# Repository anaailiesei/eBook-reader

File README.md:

# OpenBook

## 1. Diagrama Bloc

## 2. BOM
|DEVICE                                                  |PARTS                                                                                                  |PURCHASE URL                                                                                                                                      |DATASHEET URL                                                                                                                                     |
|--------------------------------------------------------|-------------------------------------------------------------------------------------------------------|--------------------------------------------------------------------------------------------------------------------------------------------------|--------------------------------------------------------------------------------------------------------------------------------------------------|
|ADAFRUIT_LEDCHIP-LED0603                                |CHG_LED                                                                                                |https://www.tme.eu/en/details/kp-1608surck/smd-colour-leds/kingbright-electronic/                                                                 |https://www.alldatasheet.com/datasheet-pdf/pdf/1153370/TO-GRACE/KP-1608SURCK.html                                                                 |
|EAGLE-LTSPICE_C                                         |EPD_C5                                                                                                 |https://www.digikey.com/en/products/detail/samsung-electro-mechanics/CL05B104KB5NNNC/11696318                                                     |https://www.digikey.com/en/products/detail/samsung-electro-mechanics/CL05B104KB5NNNC/11696318                                                     |
|ESP32_WROVER_EAGLE-LTSPICE_R                            |R3                                                                                                     |https://www.digikey.com/en/products/detail/cts-resistor-products/73L1R47J/1543472                                                                 |https://www.digikey.com/en/products/detail/cts-resistor-products/73L1R47J/1543472                                                                 |
|ESP32_WROVER_EAGLE-LTSPICE_R                            |R1_PWRUSB                                                                                              |https://www.digikey.com/en/products/detail/yageo/RC0402JR-07100KL/726416                                                                          |https://www.digikey.com/en/products/detail/yageo/RC0402JR-07100KL/726416                                                                          |
|EAGLE-LTSPICE_C                                         |C1, C2, C4_USB, C6, C8, C9, C10, C_DELAY                                                               |https://www.digikey.com/en/products/detail/samsung-electro-mechanics/CL05B104KP5NNNC/3886660                                                      |https://www.digikey.com/en/products/detail/samsung-electro-mechanics/CL05B104KP5NNNC/3886660                                                      |
|RCL_CPOL-EUCT3528                                       |C3                                                                                                     |https://ro.mouser.com/ProductDetail/KEMET/T491B107K006AT?qs=0CYHZL%252BGkuR7Fv7IsnkA2g%3D%3D                                                      |https://ro.mouser.com/ProductDetail/KEMET/T491B107K006AT?qs=0CYHZL%252BGkuR7Fv7IsnkA2g%3D%3D                                                      |
|ESP32_WROVER_EAGLE-LTSPICE_R                            |R1, R1_PINH, R1_PINH1, R2_PINH, R2_PINH1, R4, R5, R6, R7, R8, R9, R10, R_BOOT, R_CHANGE, R_CL1, R_RESET|https://www.digikey.com/en/products/detail/yageo/RC0402JR-0710KL/726418                                                                           |https://www.digikey.com/en/products/detail/yageo/RC0402JR-0710KL/726418                                                                           |
|EAGLE-LTSPICE_C                                         |C7                                                                                                     |https://www.digikey.com/en/products/detail/samsung-electro-mechanics/CL05A106MP5NUNC/3887108                                                      |https://www.digikey.com/en/products/detail/samsung-electro-mechanics/CL05A106MP5NUNC/3887108                                                      |
|112A-TAAR-R03_ATTEND                                    |J4                                                                                                     |https://www.digikey.com/en/products/detail/attend-technology/112A-TAAR-R03/17633923?s=N4IgTCBcDaIIxzAQQLQBUlIEoqwBgGYQBdAXyA                      |https://www.digikey.com/en/products/detail/attend-technology/112A-TAAR-R03/17633923?s=N4IgTCBcDaIIxzAQQLQBUlIEoqwBgGYQBdAXyA                      |
|ESP32_WROVER_EAGLE-LTSPICE_R                            |R_CAPACITOR                                                                                            |https://www.digikey.com/en/products/detail/te-connectivity-passive-product/CRGCQ0402F15R/8576207                                                  |https://www.digikey.com/en/products/detail/te-connectivity-passive-product/CRGCQ0402F15R/8576207                                                  |
|EAGLE-LTSPICE_C                                         |C5                                                                                                     |https://www.digikey.com/en/products/detail/taiyo-yuden/JMK105BJ105KV-F/930583                                                                     |https://www.digikey.com/en/products/detail/taiyo-yuden/JMK105BJ105KV-F/930583                                                                     |
|EAGLE-LTSPICE_C                                         |EPD_C1, EPD_C2, EPD_C3, EPD_C4, EPD_C6, EPD_C7, EPD_C8, EPD_C9, EPD_C10                                |https://www.digikey.com/en/products/detail/murata-electronics/GRM155R61H105KE05D/13531808                                                         |https://www.digikey.com/en/products/detail/murata-electronics/GRM155R61H105KE05D/13531808                                                         |
|ESP32_WROVER_EAGLE-LTSPICE_R                            |R2                                                                                                     |https://www.digikey.com/en/products/detail/stackpole-electronics-inc/RMCF0402FT2R20/4376617                                                       |https://www.digikey.com/en/products/detail/stackpole-electronics-inc/RMCF0402FT2R20/4376617                                                       |
|ESP32_WROVER_EAGLE-LTSPICE_R                            |R1_BAT                                                                                                 |https://www.digikey.com/en/products/detail/panasonic-electronic-components/ERJ-2RKF2000X/192215                                                   |https://www.digikey.com/en/products/detail/panasonic-electronic-components/ERJ-2RKF2000X/192215                                                   |
|ESP32_WROVER_SPARKFUN-DISCRETESEMI_MOSFET_PCH           |Q1, Q2                                                                                                 |https://ro.mouser.com/ProductDetail/Diodes-Incorporated/DMG2305UXQ-7?qs=60RJRzIpcl%2FUiAojHt1c9w%3D%3D                                            |https://ro.mouser.com/ProductDetail/Diodes-Incorporated/DMG2305UXQ-7?qs=60RJRzIpcl%2FUiAojHt1c9w%3D%3D                                            |
|ESP32_WROVER_EAGLE-LTSPICE_R                            |R2_BAT                                                                                                 |https://www.digikey.com/en/products/detail/panasonic-electronic-components/ERJ-2RKF2001X/192194                                                   |https://www.digikey.com/en/products/detail/panasonic-electronic-components/ERJ-2RKF2001X/192194                                                   |
|EAGLE-LTSPICE_C                                         |C1_BAT, C1_BAT1, C1_BAT2, C2_BAT, C5_USB                                                               |https://www.digikey.com/en/products/detail/samsung-electro-mechanics/CL05A475KQ5NRNC/3887139                                                      |https://www.digikey.com/en/products/detail/samsung-electro-mechanics/CL05A475KQ5NRNC/3887139                                                      |
|EAGLE-LTSPICE_C                                         |C4                                                                                                     |https://www.digikey.com/en/products/detail/murata-electronics/GRM155C61E475ME15D/16821133                                                         |https://www.digikey.com/en/products/detail/murata-electronics/GRM155C61E475ME15D/16821133                                                         |
|ESP32_WROVER_EAGLE-LTSPICE_R                            |R2-USB, R2-USB1                                                                                        |https://www.digikey.com/en/products/detail/panasonic-electronic-components/ERA-2AEB512X/1706022                                                   |https://www.digikey.com/en/products/detail/panasonic-electronic-components/ERA-2AEB512X/1706022                                                   |
|744043680IND_4828-WE-TPC_WRE                            |L1                                                                                                     |https://www.digikey.com/en/products/detail/w%C3%BCrth-elektronik/744043680/1638515?s=N4IgTCBcDaIOwBYEAYEGYBsAOZIC6AvkA                            |https://www.digikey.com/en/products/detail/w%C3%BCrth-elektronik/744043680/1638515?s=N4IgTCBcDaIOwBYEAYEGYBsAOZIC6AvkA                            |
|BD5229G-TR                                              |IC1                                                                                                    |https://www.digikey.com/en/products/detail/rohm-semiconductor/BD5229G-TR/658502?s=N4IgTCBcDaIEIBECsYwE4DiBaAKgJRAF0BfIA                           |https://www.digikey.com/en/products/detail/rohm-semiconductor/BD5229G-TR/658502?s=N4IgTCBcDaIEIBECsYwE4DiBaAKgJRAF0BfIA                           |
|ESP32_WROVER_BME680_BME680                              |SENSOR2                                                                                                |https://www.digikey.com/en/products/detail/bosch-sensortec/BME680/7401317                                                                         |https://www.digikey.com/en/products/detail/bosch-sensortec/BME680/7401317                                                                         |
|BUTTON_CUSYOMV1.                                        |BOOT_BUTTON, CHANGE_BUTTON, RESET_BUTTON                                                               |https://www.digikey.com/en/products/detail/c-k/KMS221G-LFS/2043218?s=N4IgTCBcDaINIFkDKYwEYDiAZAYkkAugL5A                                          |https://www.digikey.com/en/products/detail/c-k/KMS221G-LFS/2043218?s=N4IgTCBcDaINIFkDKYwEYDiAZAYkkAugL5A                                          |
|CPH3225A                                                |C10_SUPERCAP                                                                                           |https://www.snapeda.com/api/url_track_click_mouser/?unipart_id=562593&manufacturer=Seiko Instruments&part_name=CPH3225A&search_term=None          |https://www.snapeda.com/api/url_track_click_mouser/?unipart_id=562593&manufacturer=Seiko Instruments&part_name=CPH3225A&search_term=None          |
|DS3231SN#                                               |U3                                                                                                     |https://www.snapeda.com/api/url_track_click_mouser/?unipart_id=99048&manufacturer=Analog Devices&part_name=DS3231SN#&search_term=None             |https://www.snapeda.com/api/url_track_click_mouser/?unipart_id=99048&manufacturer=Analog Devices&part_name=DS3231SN#&search_term=None             |
|ESP32-C6-WROOM-1-N8                                     |U2                                                                                                     |https://www.digikey.com/en/products/detail/espressif-systems/ESP32-C6-WROOM-1-N8/17728866?s=N4IgTCBcDaIKIGUAKBmMBaAwgNnQdQCUB5IgWXQEZ0A5ADhAF0BfIA|https://www.digikey.com/en/products/detail/espressif-systems/ESP32-C6-WROOM-1-N8/17728866?s=N4IgTCBcDaIKIGUAKBmMBaAwgNnQdQCUB5IgWXQEZ0A5ADhAF0BfIA|
|ESP32C6_VARISTORCN1812                                  |PFMF.050.1                                                                                             |https://www.digikey.com/en/products/detail/epcos-tdk-electronics/B72580T0400K062/4945372                                                          |https://www.digikey.com/en/products/detail/epcos-tdk-electronics/B72580T0400K062/4945372                                                          |
|ESP32_WROVER_AVX---SD0805S020S1R0_AVX_SD0805S020S1R0_0_0|D2                                                                                                     |https://www.digikey.com/en/products/detail/kyocera-avx/SD0805S020S1R0/3749517?s=N4IgTCBcDaIMoBEAMAOJBWOSxLgRgCUkQBdAXyA                           |https://www.digikey.com/en/products/detail/kyocera-avx/SD0805S020S1R0/3749517?s=N4IgTCBcDaIMoBEAMAOJBWOSxLgRgCUkQBdAXyA                           |
|ESP32_WROVER_SPARKFUN-IC-POWER_MCP73831                 |MCP73831                                                                                               |https://www.digikey.com/en/products/detail/microchip-technology/MCP73831T-2ACI-OT/964301                                                          |https://www.digikey.com/en/products/detail/microchip-technology/MCP73831T-2ACI-OT/964301                                                          |
|FH34SRJ-24S-0.5SH_99_                                   |J1                                                                                                     |https://www.digikey.com/en/products/detail/hirose-electric-co-ltd/fh34srj-24s-0-5sh-99/5132529                                                    |https://www.digikey.com/en/products/detail/hirose-electric-co-ltd/fh34srj-24s-0-5sh-99/5132529                                                    |
|MAX17048G+T10                                           |U4                                                                                                     |https://www.snapeda.com/api/url_track_click_mouser/?unipart_id=329239&manufacturer=Analog Devices&part_name=MAX17048G+T10&search_term=None        |https://www.digikey.com/en/products/detail/analog-devices-inc-maxim-integrated/max17048g-t10/3758921                                              |
|MBR0530.                                                |D3, D4, D5                                                                                             |https://www.digikey.com/en/products/detail/smc-diode-solutions/MBR0530/16692306                                                                   |https://www.digikey.com/en/products/detail/smc-diode-solutions/MBR0530/16692306                                                                   |
|PGB1010603MR.                                           |D6, D8, D9, D10, D11, D12                                                                              |https://www.digikey.com/en/products/detail/littelfuse-inc/PGB1010603MR/715755                                                                     |https://www.digikey.com/en/products/detail/littelfuse-inc/PGB1010603MR/715755                                                                     |
|QWIIC_CONNECTORJS-1MM                                   |J3                                                                                                     |https://www.digikey.lt/en/products/detail/jst-sales-america-inc/SM04B-SRSS-TB/926710                                                              |https://www.digikey.lt/en/products/detail/jst-sales-america-inc/SM04B-SRSS-TB/926710                                                              |
|SAMACSYS_PARTS_USB4110-GF-A                             |J2                                                                                                     |https://www.digikey.lt/en/products/detail/gct/usb4110-gf-a/10384547                                                                               |https://www.digikey.lt/en/products/detail/gct/usb4110-gf-a/10384547                                                                               |
|ESP32_WROVER_AVX---SD0805S020S1R0_AVX_SD0805S020S1R0_0_0|D7                                                                                                     |https://www.digikey.lt/en/products/detail/kyocera-avx/sd0805s020s1r0/3749517                                                                      |https://www.digikey.lt/en/products/detail/kyocera-avx/sd0805s020s1r0/3749517                                                                      |
|SI1308EDL-T1-GE3                                        |Q3                                                                                                     |https://www.digikey.lt/en/products/detail/vishay-siliconix/si1308edl-t1-ge3/4876435                                                               |https://www.digikey.lt/en/products/detail/vishay-siliconix/si1308edl-t1-ge3/4876435                                                               |
|USBLC6-2SC6Y                                            |D1                                                                                                     |https://www.digikey.lt/en/products/detail/stmicroelectronics/usblc6-2sc6y/2819177                                                                 |https://www.digikey.lt/en/products/detail/stmicroelectronics/usblc6-2sc6y/2819177                                                                 |
|W25Q512JVEIQ                                            |U1                                                                                                     |https://www.digikey.lt/en/products/detail/winbond-electronics/w25q512jveiq/10244706                                                               |https://www.digikey.lt/en/products/detail/winbond-electronics/w25q512jveiq/10244706                                                               |
|XC6220A331MR-G                                          |IC4                                                                                                    |https://www.digikey.lt/en/products/detail/torex-semiconductor-ltd/xc6220a331mr-g/10165775                                                         |https://www.digikey.lt/en/products/detail/torex-semiconductor-ltd/xc6220a331mr-g/10165775                                                         |
|TP                                                      |TP1, TP2, TP3, TP4, TP5, TP6, TP7, TP8, TP9, TP10, TP11, TP12, TP13, TP14, TP15, TP16, TP17            |                                                                                                                                                  |                                                                                                                                                  |
|SJ                                                      |SJ1                                                                                                    |                                                                                                                                                  |                                                                                                                                                  |

## 3. Descrierea în detaliu a funcționalității hardware
| Nume       | Descriere                                                                  | Pini comunicare ESP32-C6     | Comunicare     |
|------------------------|-------------------------------------------------------------------------------|---------------------------|----------------|
| ESP32-C6-WROOM-1       | MCU RISC-V pe 32 de biți la 160MHz, cu memorie SRAM de 512KB + 16KB și flash extern de 8MB                                                    | USB 2.0, SPI, I2C, UART, GPIO | -              |
| 7.5" e-Paper Display   | E-Paper de 7.5 inch, 800x480 pixeli, alb-negru, cu contrast 8:1, refresh rapid (sub 1s)                                             | SPI + CS, DC, RST, BUSY   | SPI            |
| BME688 Sensor          | Senzor  pentru temperatură, umiditate, presiune și calitatea aerului                                  | SDA, SCL       | I2C            |
| MAX17048 Fuel Gauge    | Gestionare baterie                                                         | I2C                       | I2C            |
| MCP73831 Charger       | Gestionare baterie                                                               | GPIO for control          | GPIO           |
| Buttons        | Butoane fizice tactile cu debouncing hardware prin filtre RC                                              | 3x GPIOs                  | GPIO           |
| USB-C Connector        | Pentru încărcare și transfer de date USB 2.0, cu protecție ESD și posibil suport pentru Power Delivery                                  | USB-D+/D- (native USB)    | USB            |
| SD Card Connector      | Pentru memorie                                                              | - | SPI     |
| DS3231 RTC             | Ceas Real Time                                          | I2C                       | I2C            |
| Qwiic/Stemma Connector | Expansiune conector senzori                                               | I2C                | I2C            |
| LDO Voltage Regulator  | Genereaza o singură șină de alimentare de 3.3V                                             | -                         | -          |
| Baterie (2500mAh)      | Baterie Li-Polimer de 2500mAh, 3.7V. Consum redus în deep sleep (sub 50µA) și alimentare de 3.3V pentru sistem                                                  | -                         | -          |

## 4. Asezarea componentelor in carcasa

* PCB-ul are o grosime de 1mm si este sprijinit de capacul carcasei
* Bateria este sprijinita de capacul carcasei
* Ecranul este sprijinit de spatele PCB-ului

## 5. Pasi de implementare
1. Am realizat schematicul cu ajutor componentelor din libraria data si schematicul model.
2. De la schematic am generat PCB-ul 2D. Am adaugat componentele pe PCB conform schemei date.
3. Am facut un nou net class pentru liniile de putere (SupplyNets) si am adaugat liniile corespunzatoare. Am facut o regula speciala pentru grosimea acestor linii (0.3mm).
4. Am rutat manual liniile de putere pentru a ma asigura ca nu folosesc vias-uri prea multe (a fost necesar sa folosesc vias-uri o singura data). Am facut apoi autorutarea.
5. Am adaugat planurile de masa si via stiches.
6. Am adaugat pentru fiecare componenta un model 3D. Am tinut cont la elementele polarizate sau marcate de orientarea componentei pentru o reprezentare cat mai realista.
7. Am modelat bateria si ecranul conform datasheetului si le-am asamblat in carcasa.

## 6. Decizii

* Eroare SMD-Hole (Samacsys-Parts): Am rezolvat mutand gaurile cu 0.1 mm.

* Eroare Copper width SMD (Net Class: SupplyLines): Am modificat pad-urile de la bobina (Ind_4828) sa fie mai mari (0.5 x 0.5 mm) ca sa permita conectarea cu liniile de putere.

* Eroare Copper width SMD (Net Class: SupplyLines): Am modificat pad-urile de la SON50P200X sa fie mai mari (de la 0.27 mm la 0.3 mm) ca sa permita conectarea cu liniile de putere (VBAT).

* Am aprobat erorile de Power Pin ... connected to ... din Schematic.

## 7. Dificultati
* Gasirea modelelor 3D pentru fiecare componenta, actualizarea bibliotecii, aranjarea lor sa se potriveasca cu footprint-ul.
* M-am asigurat ca nu am froarte multe vias-uri la traseele de putere si a trebuit sa fac o parte din rutare manual. Nu am putut evita o situatie (traseele ar fi ajuns sa fie exagerat de lungi din cauza ocolirilor daca nu foloseam) si a fost nevoie sa folosesc vias-uri pe un traseu de putere.
* Desi nu am avut de facut modele 3D complexe, aceasta a fost o provocare deoarece a fost prima data cand am facut asa ceva.
* Verificarea ca traseele sa nu contina unghiuri drepte si corectarea lor.

## 8. Imagini PCB

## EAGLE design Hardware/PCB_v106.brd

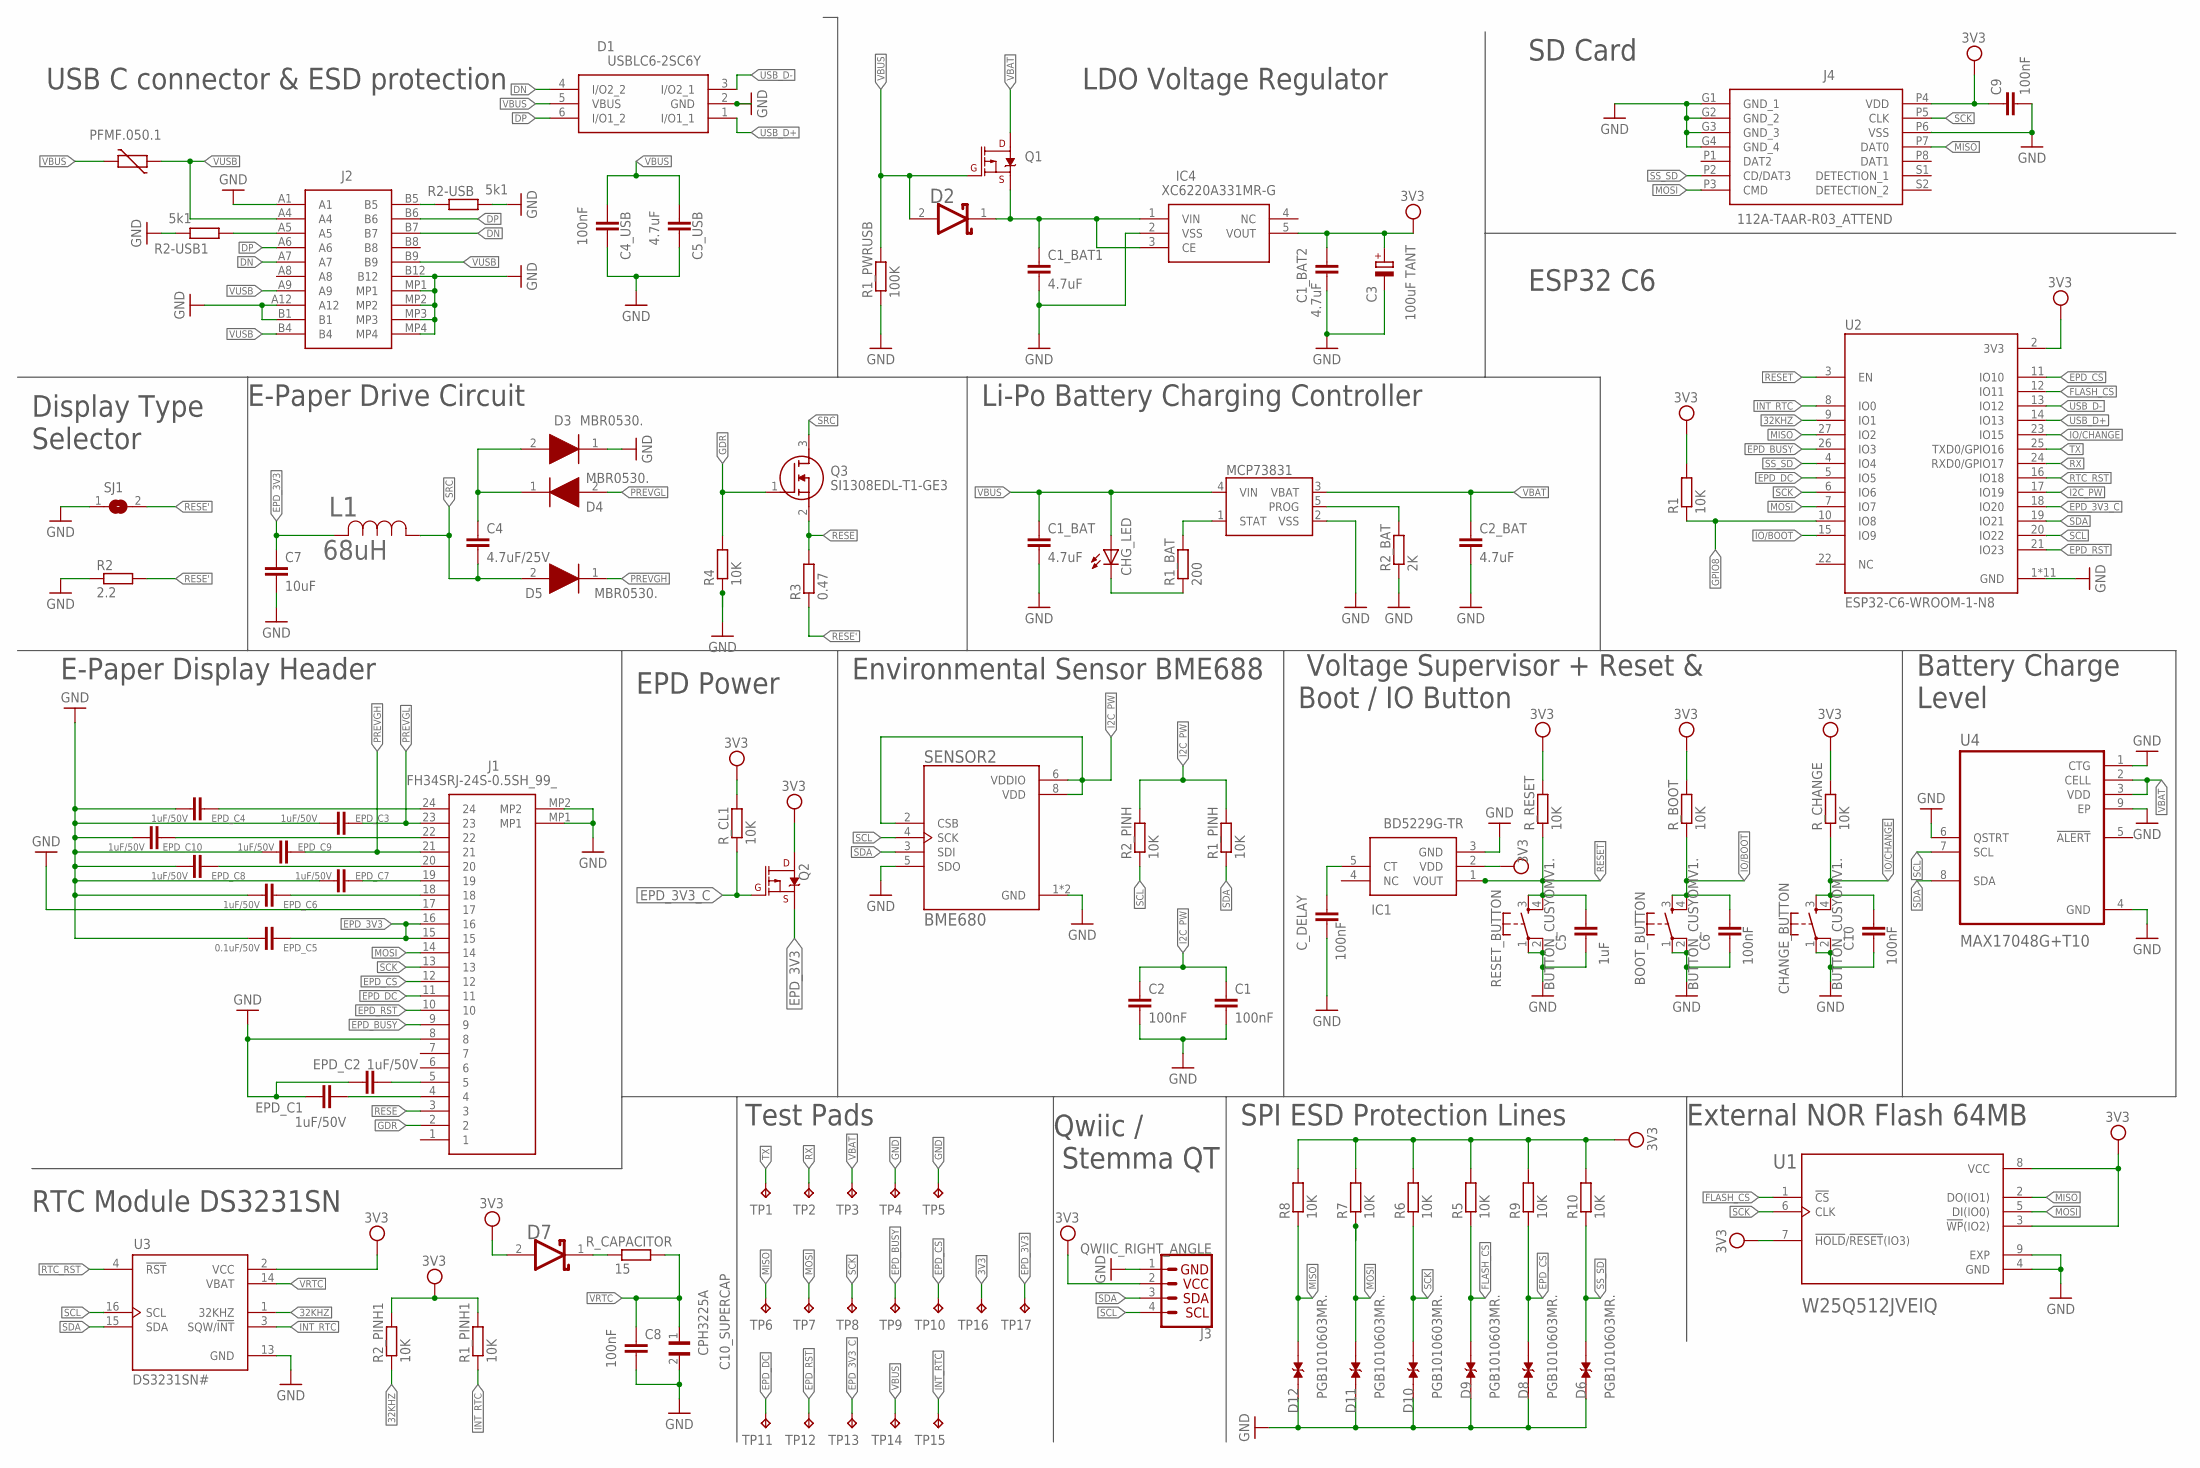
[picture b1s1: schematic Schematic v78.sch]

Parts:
BOOT_BUTTON: BUTTON_CUSYOMV1.; MYBUTTON
C1, C2, C4_USB, C6, C8, C9, C10: 100nF; EAGLE-LTSPICE_C0402
C1_BAT, C1_BAT1, C1_BAT2, C2_BAT, C5_USB: 4.7uF; EAGLE-LTSPICE_C0402
C3: 100uF TANT; RCL_CT3528
C4: 4.7uF/25V; EAGLE-LTSPICE_C0402
C5: 1uF; EAGLE-LTSPICE_C0402
C7: 10uF; EAGLE-LTSPICE_C0402
C10_SUPERCAP: CPH3225A; CAPCP3225X100N
CHANGE_BUTTON: BUTTON_CUSYOMV1.; MYBUTTON
CHG_LED: ADAFRUIT_LEDCHIP-LED0603; ADAFRUIT_CHIP-LED0603
C_DELAY: 100nF; EAGLE-LTSPICE_C0402
D1: USBLC6-2SC6Y; SOT95P280X145-6N
D2: ESP32_WROVER_AVX---SD0805S020S1R0_AVX_SD0805S020S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; ESP32_WROVER_AVX---SD0805S020S1R0_AVX_SD0805S020S1R0_0
D3, D4, D5: MBR0530.; SOD3716X135N
D6, D8, D9, D10, D11, D12: PGB1010603MR.; DIOC1608X36N
D7: SD0805S020S1R0; ESP32_WROVER_AVX---SD0805S020S1R0_AVX_SD0805S020S1R0_0
EPD_C1, EPD_C2, EPD_C3, EPD_C4, EPD_C6, EPD_C7, EPD_C8, EPD_C9, EPD_C10: 1uF/50V; EAGLE-LTSPICE_C0402
EPD_C5: 0.1uF/50V; EAGLE-LTSPICE_C0402
IC1: BD5229G-TR; SOT95P280X125-5N
IC4: XC6220A331MR-G; SOT95P280X120-5N
J1: FH34SRJ-24S-0.5SH_99_; FH34SRJ24S05SH99
J2: SAMACSYS_PARTS_USB4110-GF-A; SAMACSYS_PARTS_USB4110GFA
J3: QWIIC_RIGHT_ANGLE; JST04_1MM_RA
J4: 112A-TAAR-R03_ATTEND; 112ATAARR03ATTEND
L1: 68uH; IND_4828-WE-TPC_WRE
MCP73831: ESP32_WROVER_SPARKFUN-IC-POWER_MCP73831; ESP32_WROVER_SPARKFUN-IC-POWER_SOT23-5
PFMF.050.1: ESP32C6_VARISTORCN1812; ESP32C6_VARISTOR_CT/CN1812
Q1, Q2: 20V/4.2A/52mΩ/1.4W; ESP32_WROVER_SPARKFUN-DISCRETESEMI_SOT23-3
Q3: SI1308EDL-T1-GE3; SOT65P210X110-3N
R1, R1_PINH, R1_PINH1, R2_PINH, R2_PINH1, R4, R5, R6, R7, R8, R9, R10: 10K; ESP32_WROVER_EAGLE-LTSPICE_R0402
R1_BAT: 200; ESP32_WROVER_EAGLE-LTSPICE_R0402
R1_PWRUSB: 100K; ESP32_WROVER_EAGLE-LTSPICE_R0402
R2: 2.2; ESP32_WROVER_EAGLE-LTSPICE_R0402
R2-USB, R2-USB1: 5k1; ESP32_WROVER_EAGLE-LTSPICE_R0402
R2_BAT: 2K; ESP32_WROVER_EAGLE-LTSPICE_R0402
R3: 0.47; ESP32_WROVER_EAGLE-LTSPICE_R0402
RESET_BUTTON: BUTTON_CUSYOMV1.; MYBUTTON
R_BOOT: 10K; ESP32_WROVER_EAGLE-LTSPICE_R0402
R_CAPACITOR: 15; ESP32_WROVER_EAGLE-LTSPICE_R0402
R_CHANGE: 10K; ESP32_WROVER_EAGLE-LTSPICE_R0402
R_CL1: 10K; ESP32_WROVER_EAGLE-LTSPICE_R0402
R_RESET: 10K; ESP32_WROVER_EAGLE-LTSPICE_R0402
SENSOR2: BME680; ESP32_WROVER_BME680_PSON80P300X300X100-8N
SJ1: SJ
TP1: TX; TP20R
TP2: RX; TP20R
TP3: VBAT; TP20R
TP4, TP5: GND; TP20R
TP6: MISO; TP20R
TP7: MOSI; TP20R
TP8: SCK; TP20R
TP9: EPD_BUSY; TP20R
TP10: EPD_CS; TP20R
TP11: EPD_DC; TP20R
TP12: EPD_RST; TP20R
TP13: EPD_3V3_C; TP20R
TP14: VBUS; TP20R
TP15: INT_RTC; TP20R
TP16: 3V3; TP20R
TP17: EPD_3V3; TP20R
U1: W25Q512JVEIQ; SON127P600X800X80-9N
U2: ESP32-C6-WROOM-1-N8; XCVR_ESP32-C6-WROOM-1-N8
U3: DS3231SN#; SOIC127P1032X265-16N
U4: MAX17048G+T10; SON50P200X200X80-9N

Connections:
3V3: C1_BAT2.1, C3.+, C9.1, D7.2 (ANODE), IC1.2 (VDD), IC4.5 (VOUT), J3.2, J4.P4 (VDD), Q2.3 (D), R1.2, R1_PINH1.2, R2_PINH1.2, R5.2, R6.2, R7.2, R8.2, R9.2, R10.2, R_BOOT.2, R_CHANGE.2, R_CL1.2, R_RESET.2, TP16.TP, U1.3 (!WP!(IO2)), U1.7 (!HOLD!/!RESET!(IO3)), U1.8 (VCC), U2.2 (3V3), U3.2 (VCC)
32KHZ: R2_PINH1.1, U2.9 (IO1), U3.1 (32KHZ)
DN: D1.4 (I/O2_2), J2.A7, J2.B7
DP: D1.6 (I/O1_2), J2.A6, J2.B6
EPD_3V3: C7.1, EPD_C5.2, J1.15, J1.16, L1.2, Q2.2 (S), TP17.TP
EPD_3V3_C: Q2.1 (G), R_CL1.1, TP13.TP, U2.18 (IO20)
EPD_BUSY: J1.9, TP9.TP, U2.26 (IO3)
EPD_CS: D8.2, J1.12, R9.1, TP10.TP, U2.11 (IO10)
EPD_DC: J1.11, TP11.TP, U2.5 (IO5)
EPD_RST: J1.10, TP12.TP, U2.21 (IO23)
FLASH_CS: D9.2, R5.1, U1.1 (!CS), U2.12 (IO11)
GDR: J1.2, Q3.1 (G), R4.2
GND: BOOT_BUTTON.1, BOOT_BUTTON.2, C1.2, C1_BAT.2, C1_BAT1.2, C1_BAT2.2, C2.2, C2_BAT.2, C3.-, C4_USB.2, C5.2, C5_USB.2, C6.2, C7.2, C8.2, C9.2, C10.2, C10_SUPERCAP.2, CHANGE_BUTTON.1, CHANGE_BUTTON.2, C_DELAY.2, D1.2 (GND), D3.1 (K), D6.1, D8.1, D9.1, D10.1, D11.1, D12.1, EPD_C1.1, EPD_C2.1, EPD_C3.1, EPD_C4.1, EPD_C5.1, EPD_C6.1, EPD_C7.1, EPD_C8.1, EPD_C9.1, EPD_C10.1, IC1.3 (GND), IC4.2 (VSS), J1.8, J1.17, J1.MP1, J1.MP2, J2.A1, J2.A12, J2.B1, J2.B12, J2.MP1, J2.MP2, J2.MP3, J2.MP4, J3.1, J4.G1 (GND_1), J4.G2 (GND_2), J4.G3 (GND_3), J4.G4 (GND_4), J4.P6 (VSS), MCP73831.2 (VSS), R1_PWRUSB.1, R2.1, R2-USB.2, R2-USB1.1, R2_BAT.1, R4.1, RESET_BUTTON.1, RESET_BUTTON.2, SENSOR2.1 (GND), SENSOR2.5 (SDO), SENSOR2.7 (GND), SJ1.1, TP4.TP, TP5.TP, U1.4 (GND), U1.9 (EXP), U2.1 (GND), U2.28 (GND), U2.29_1 (GND), U2.29_2 (GND), U2.29_3 (GND), U2.29_4 (GND), U2.29_5 (GND), U2.29_6 (GND), U2.29_7 (GND), U2.29_8 (GND), U2.29_9 (GND), U3.13 (GND), U4.1 (CTG), U4.4 (GND), U4.6 (QSTRT), U4.9 (EP)
GPIO8: R1.1, U2.10 (IO8)
I2C_PW: C1.1, C2.1, R1_PINH.2, R2_PINH.2, SENSOR2.2 (CSB), SENSOR2.6 (VDDIO), SENSOR2.8 (VDD), U2.17 (IO19)
INT_RTC: R1_PINH1.1, TP15.TP, U2.8 (IO0), U3.3 (SQW/!INT)
IO/BOOT: BOOT_BUTTON.3, BOOT_BUTTON.4, C6.1, R_BOOT.1, U2.15 (IO9)
IO/CHANGE: C10.1, CHANGE_BUTTON.3, CHANGE_BUTTON.4, R_CHANGE.1, U2.23 (IO15)
MISO: D12.2, J4.P7 (DAT0), R8.1, TP6.TP, U1.2 (DO(IO1)), U2.27 (IO2)
MOSI: D11.2, J1.14, J4.P3 (CMD), R7.1, TP7.TP, U1.5 (DI(IO0)), U2.7 (IO7)
unnamed: J2.B5, R2-USB.1
unnamed: J2.A5, R2-USB1.2
unnamed: C1_BAT1.1, D2.1 (CATHODE), IC4.1 (VIN), IC4.3 (CE), Q1.2 (S)
unnamed: C4.1, D3.2 (A), D4.1 (K)
unnamed: MCP73831.1 (STAT), R1_BAT.2
unnamed: EPD_C1.2, J1.4
unnamed: MCP73831.5 (PROG), R2_BAT.2
unnamed: CHG_LED.C, R1_BAT.1
unnamed: EPD_C2.2, J1.5
unnamed: EPD_C8.2, J1.20
unnamed: EPD_C10.2, J1.22
unnamed: C_DELAY.1, IC1.5 (CT)
unnamed: EPD_C4.2, J1.24
unnamed: D7.1 (CATHODE), R_CAPACITOR.1
unnamed: EPD_C6.2, J1.18
unnamed: EPD_C7.2, J1.19
PREVGH: D5.1 (K), EPD_C9.2, J1.21
PREVGL: D4.2 (A), EPD_C3.2, J1.23
RESE: J1.3, Q3.2 (S), R3.2
RESE': R2.2, R3.1, SJ1.2
RESET: C5.1, IC1.1 (VOUT), RESET_BUTTON.3, RESET_BUTTON.4, R_RESET.1, U2.3 (EN)
RTC_RST: U2.16 (IO18), U3.4 (!RST)
RX: TP2.TP, U2.24 (RXD0/GPIO17)
SCK: D10.2, J1.13, J4.P5 (CLK), R6.1, TP8.TP, U1.6 (CLK), U2.6 (IO6)
SCL: J3.4, R2_PINH.1, SENSOR2.4 (SCK), U2.20 (IO22), U3.16 (SCL), U4.7 (SCL)
SDA: J3.3, R1_PINH.1, SENSOR2.3 (SDI), U2.19 (IO21), U3.15 (SDA), U4.8 (SDA)
SRC: C4.2, D5.2 (A), L1.1, Q3.3 (D)
SS_SD: D6.2, J4.P2 (CD/DAT3), R10.1, U2.4 (IO4)
TX: TP1.TP, U2.25 (TXD0/GPIO16)
USB_D+: D1.1 (I/O1_1), U2.14 (IO13)
USB_D-: D1.3 (I/O2_1), U2.13 (IO12)
VBAT: C2_BAT.1, MCP73831.3 (VBAT), Q1.3 (D), TP3.TP, U4.2 (CELL), U4.3 (VDD)
VBUS: C1_BAT.1, C4_USB.1, C5_USB.1, CHG_LED.A, D1.5 (VBUS), D2.2 (ANODE), MCP73831.4 (VIN), PFMF.050.1.2, Q1.1 (G), R1_PWRUSB.2, TP14.TP
VRTC: C8.1, C10_SUPERCAP.1, R_CAPACITOR.2, U3.14 (VBAT)
VUSB: J2.A4, J2.A9, J2.B4, J2.B9, PFMF.050.1.1

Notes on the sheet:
USB C connector & ESD protection
LDO Voltage Regulator
SD Card
Display Type Selector
E-Paper Drive Circuit
Li-Po Battery Charging Controller
ESP32 C6
E-Paper Display Header
EPD Power
Environmental Sensor BME688
Voltage Supervisor + Reset & Boot / IO Button
Battery Charge Level
RTC Module DS3231SN
Test Pads
Qwiic / Stemma QT
SPI ESD Protection Lines
External NOR Flash 64MB

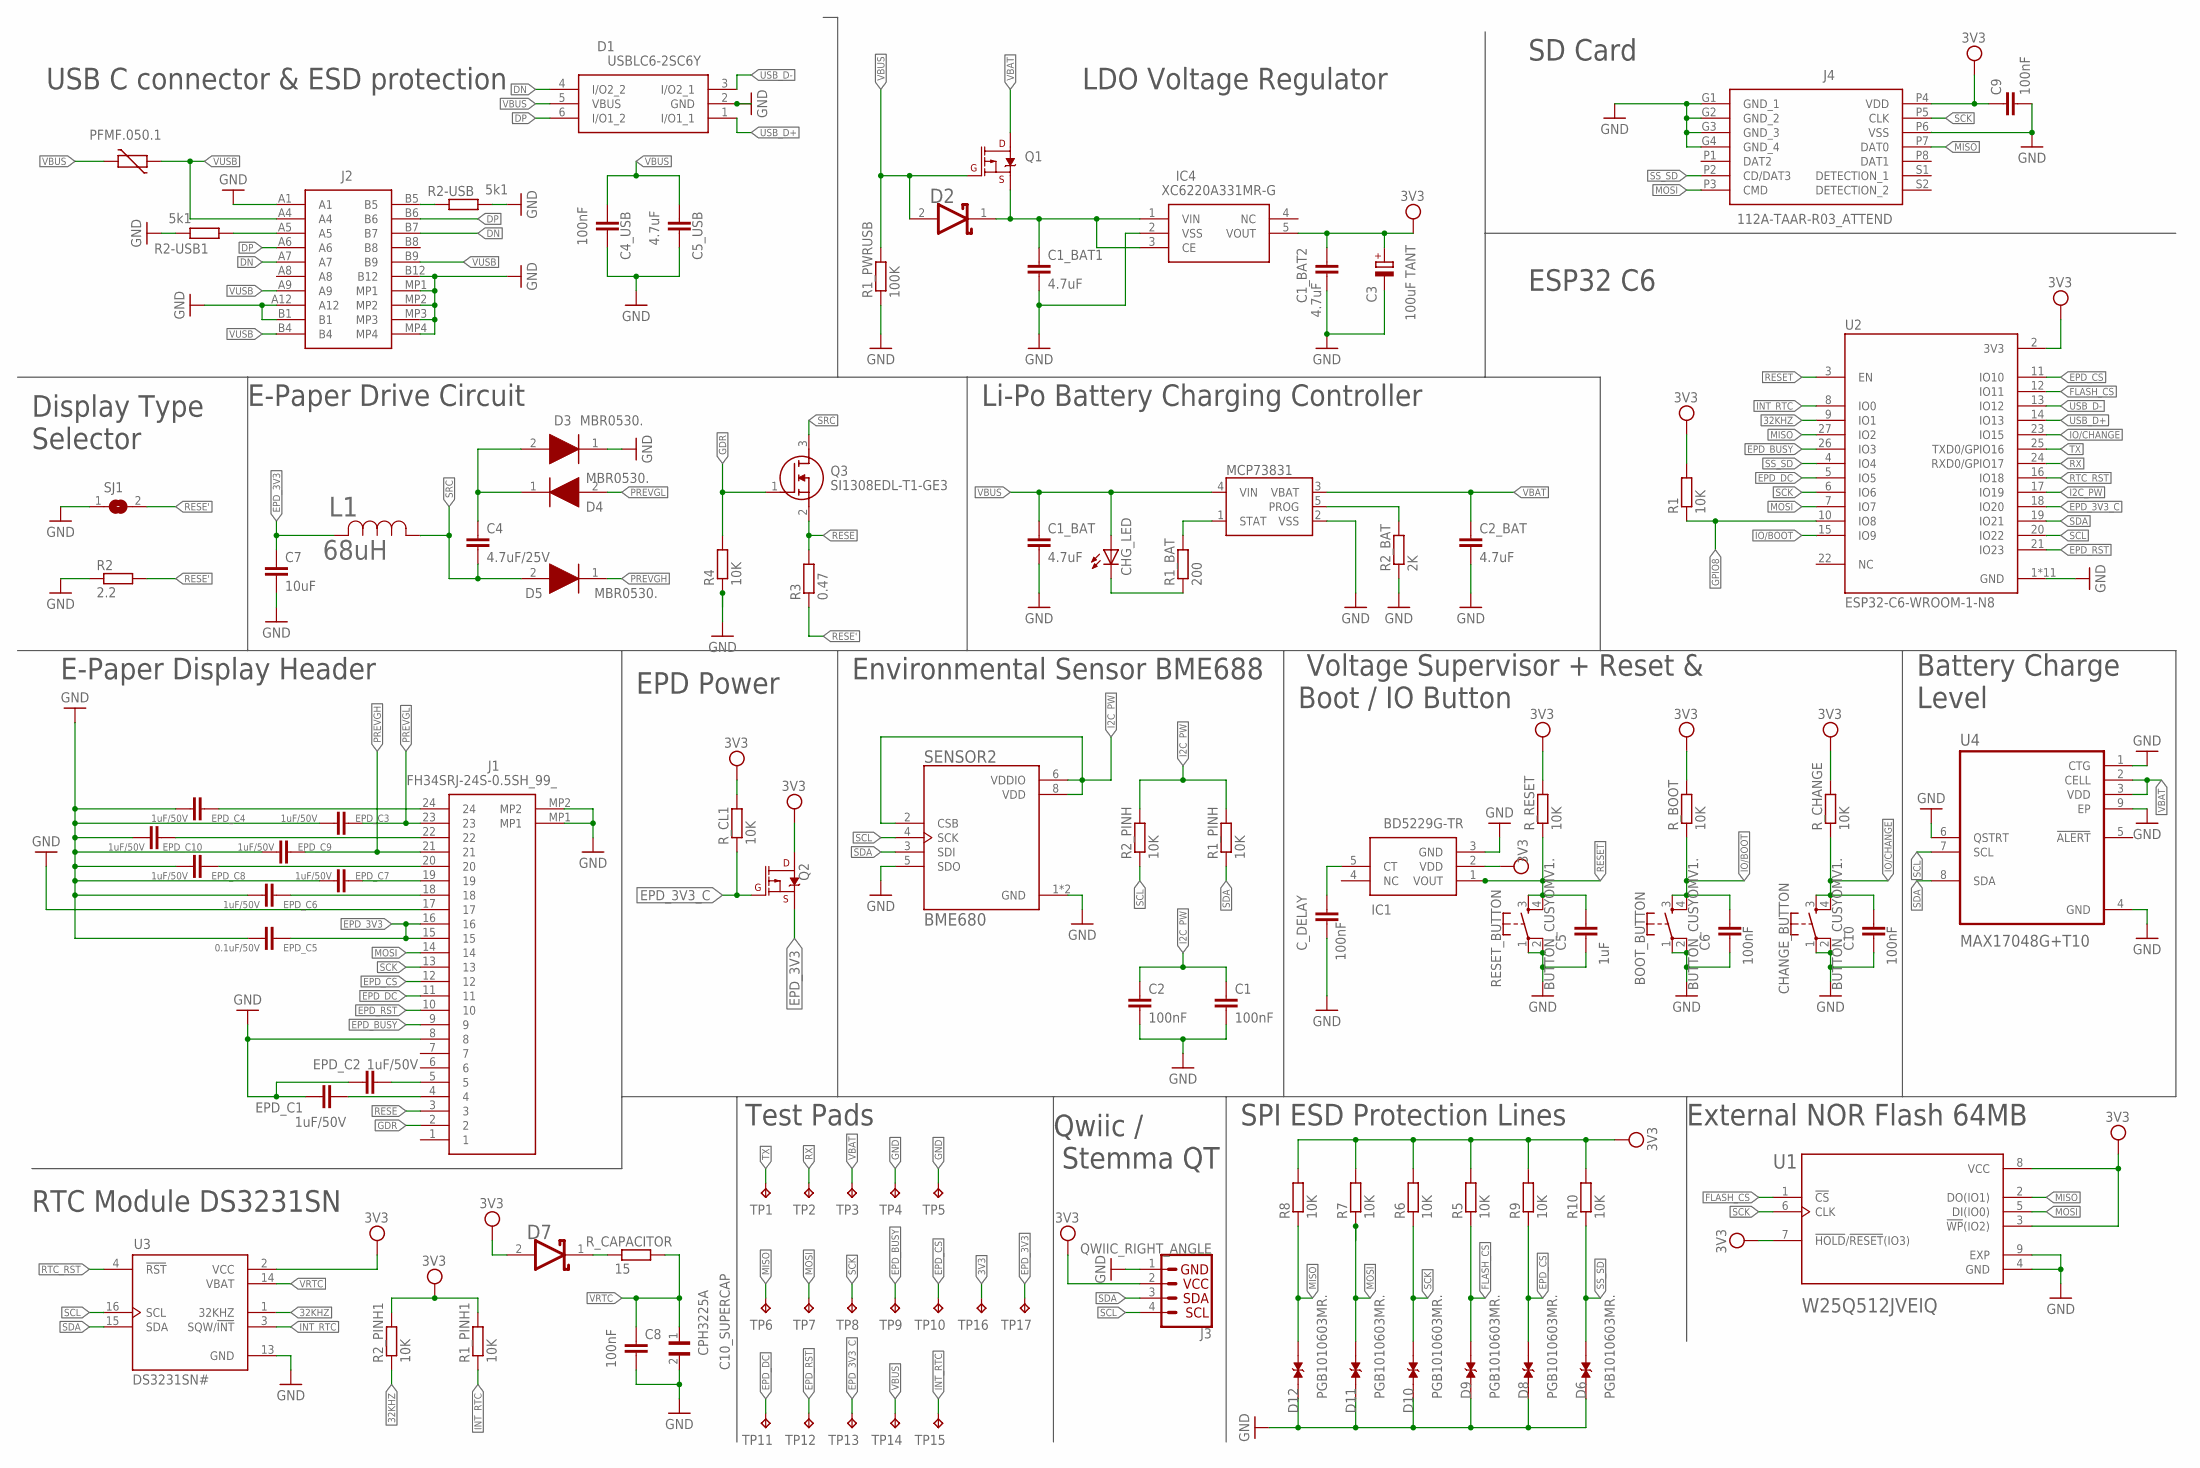
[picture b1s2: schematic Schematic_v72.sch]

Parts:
BOOT_BUTTON: BUTTON_CUSYOMV1.; MYBUTTON
C1, C2, C4_USB, C6, C8, C9, C10: 100nF; EAGLE-LTSPICE_C0402
C1_BAT, C1_BAT1, C1_BAT2, C2_BAT, C5_USB: 4.7uF; EAGLE-LTSPICE_C0402
C3: 100uF TANT; RCL_CT3528
C4: 4.7uF/25V; EAGLE-LTSPICE_C0402
C5: 1uF; EAGLE-LTSPICE_C0402
C7: 10uF; EAGLE-LTSPICE_C0402
C10_SUPERCAP: CPH3225A; CAPCP3225X100N
CHANGE_BUTTON: BUTTON_CUSYOMV1.; MYBUTTON
CHG_LED: ADAFRUIT_LEDCHIP-LED0603; ADAFRUIT_CHIP-LED0603
C_DELAY: 100nF; EAGLE-LTSPICE_C0402
D1: USBLC6-2SC6Y; SOT95P280X145-6N
D2: ESP32_WROVER_AVX---SD0805S020S1R0_AVX_SD0805S020S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; ESP32_WROVER_AVX---SD0805S020S1R0_AVX_SD0805S020S1R0_0
D3, D4, D5: MBR0530.; SOD3716X135N
D6, D8, D9, D10, D11, D12: PGB1010603MR.; DIOC1608X36N
D7: SD0805S020S1R0; ESP32_WROVER_AVX---SD0805S020S1R0_AVX_SD0805S020S1R0_0
EPD_C1, EPD_C2, EPD_C3, EPD_C4, EPD_C6, EPD_C7, EPD_C8, EPD_C9, EPD_C10: 1uF/50V; EAGLE-LTSPICE_C0402
EPD_C5: 0.1uF/50V; EAGLE-LTSPICE_C0402
IC1: BD5229G-TR; SOT95P280X125-5N
IC4: XC6220A331MR-G; SOT95P280X120-5N
J1: FH34SRJ-24S-0.5SH_99_; FH34SRJ24S05SH99
J2: SAMACSYS_PARTS_USB4110-GF-A; SAMACSYS_PARTS_USB4110GFA
J3: QWIIC_RIGHT_ANGLE; JST04_1MM_RA
J4: 112A-TAAR-R03_ATTEND; 112ATAARR03ATTEND
L1: 68uH; IND_4828-WE-TPC_WRE
MCP73831: ESP32_WROVER_SPARKFUN-IC-POWER_MCP73831; ESP32_WROVER_SPARKFUN-IC-POWER_SOT23-5
PFMF.050.1: ESP32C6_VARISTORCN1812; ESP32C6_VARISTOR_CT/CN1812
Q1, Q2: 20V/4.2A/52mΩ/1.4W; ESP32_WROVER_SPARKFUN-DISCRETESEMI_SOT23-3
Q3: SI1308EDL-T1-GE3; SOT65P210X110-3N
R1, R1_PINH, R1_PINH1, R2_PINH, R2_PINH1, R4, R5, R6, R7, R8, R9, R10: 10K; ESP32_WROVER_EAGLE-LTSPICE_R0402
R1_BAT: 200; ESP32_WROVER_EAGLE-LTSPICE_R0402
R1_PWRUSB: 100K; ESP32_WROVER_EAGLE-LTSPICE_R0402
R2: 2.2; ESP32_WROVER_EAGLE-LTSPICE_R0402
R2-USB, R2-USB1: 5k1; ESP32_WROVER_EAGLE-LTSPICE_R0402
R2_BAT: 2K; ESP32_WROVER_EAGLE-LTSPICE_R0402
R3: 0.47; ESP32_WROVER_EAGLE-LTSPICE_R0402
RESET_BUTTON: BUTTON_CUSYOMV1.; MYBUTTON
R_BOOT: 10K; ESP32_WROVER_EAGLE-LTSPICE_R0402
R_CAPACITOR: 15; ESP32_WROVER_EAGLE-LTSPICE_R0402
R_CHANGE: 10K; ESP32_WROVER_EAGLE-LTSPICE_R0402
R_CL1: 10K; ESP32_WROVER_EAGLE-LTSPICE_R0402
R_RESET: 10K; ESP32_WROVER_EAGLE-LTSPICE_R0402
SENSOR2: BME680; ESP32_WROVER_BME680_PSON80P300X300X100-8N
SJ1: SJ
TP1: TX; TP20R
TP2: RX; TP20R
TP3: VBAT; TP20R
TP4, TP5: GND; TP20R
TP6: MISO; TP20R
TP7: MOSI; TP20R
TP8: SCK; TP20R
TP9: EPD_BUSY; TP20R
TP10: EPD_CS; TP20R
TP11: EPD_DC; TP20R
TP12: EPD_RST; TP20R
TP13: EPD_3V3_C; TP20R
TP14: VBUS; TP20R
TP15: INT_RTC; TP20R
TP16: 3V3; TP20R
TP17: EPD_3V3; TP20R
U1: W25Q512JVEIQ; SON127P600X800X80-9N
U2: ESP32-C6-WROOM-1-N8; XCVR_ESP32-C6-WROOM-1-N8
U3: DS3231SN#; SOIC127P1032X265-16N
U4: MAX17048G+T10; SON50P200X200X80-9N

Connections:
3V3: C1_BAT2.1, C3.+, C9.1, D7.2 (ANODE), IC1.2 (VDD), IC4.5 (VOUT), J3.2, J4.P4 (VDD), Q2.3 (D), R1.2, R1_PINH1.2, R2_PINH1.2, R5.2, R6.2, R7.2, R8.2, R9.2, R10.2, R_BOOT.2, R_CHANGE.2, R_CL1.2, R_RESET.2, TP16.TP, U1.3 (!WP!(IO2)), U1.7 (!HOLD!/!RESET!(IO3)), U1.8 (VCC), U2.2 (3V3), U3.2 (VCC)
32KHZ: R2_PINH1.1, U2.9 (IO1), U3.1 (32KHZ)
DN: D1.4 (I/O2_2), J2.A7, J2.B7
DP: D1.6 (I/O1_2), J2.A6, J2.B6
EPD_3V3: C7.1, EPD_C5.2, J1.15, J1.16, L1.2, Q2.2 (S), TP17.TP
EPD_3V3_C: Q2.1 (G), R_CL1.1, TP13.TP, U2.18 (IO20)
EPD_BUSY: J1.9, TP9.TP, U2.26 (IO3)
EPD_CS: D8.2, J1.12, R9.1, TP10.TP, U2.11 (IO10)
EPD_DC: J1.11, TP11.TP, U2.5 (IO5)
EPD_RST: J1.10, TP12.TP, U2.21 (IO23)
FLASH_CS: D9.2, R5.1, U1.1 (!CS), U2.12 (IO11)
GDR: J1.2, Q3.1 (G), R4.2
GND: BOOT_BUTTON.1, BOOT_BUTTON.2, C1.2, C1_BAT.2, C1_BAT1.2, C1_BAT2.2, C2.2, C2_BAT.2, C3.-, C4_USB.2, C5.2, C5_USB.2, C6.2, C7.2, C8.2, C9.2, C10.2, C10_SUPERCAP.2, CHANGE_BUTTON.1, CHANGE_BUTTON.2, C_DELAY.2, D1.2 (GND), D3.1 (K), D6.1, D8.1, D9.1, D10.1, D11.1, D12.1, EPD_C1.1, EPD_C2.1, EPD_C3.1, EPD_C4.1, EPD_C5.1, EPD_C6.1, EPD_C7.1, EPD_C8.1, EPD_C9.1, EPD_C10.1, IC1.3 (GND), IC4.2 (VSS), J1.8, J1.17, J1.MP1, J1.MP2, J2.A1, J2.A12, J2.B1, J2.B12, J2.MP1, J2.MP2, J2.MP3, J2.MP4, J3.1, J4.G1 (GND_1), J4.G2 (GND_2), J4.G3 (GND_3), J4.G4 (GND_4), J4.P6 (VSS), MCP73831.2 (VSS), R1_PWRUSB.1, R2.1, R2-USB.2, R2-USB1.1, R2_BAT.1, R4.1, RESET_BUTTON.1, RESET_BUTTON.2, SENSOR2.1 (GND), SENSOR2.5 (SDO), SENSOR2.7 (GND), SJ1.1, TP4.TP, TP5.TP, U1.4 (GND), U1.9 (EXP), U2.1 (GND), U2.28 (GND), U2.29_1 (GND), U2.29_2 (GND), U2.29_3 (GND), U2.29_4 (GND), U2.29_5 (GND), U2.29_6 (GND), U2.29_7 (GND), U2.29_8 (GND), U2.29_9 (GND), U3.13 (GND), U4.1 (CTG), U4.4 (GND), U4.6 (QSTRT), U4.9 (EP)
GPIO8: R1.1, U2.10 (IO8)
I2C_PW: C1.1, C2.1, R1_PINH.2, R2_PINH.2, SENSOR2.2 (CSB), SENSOR2.6 (VDDIO), SENSOR2.8 (VDD), U2.17 (IO19)
INT_RTC: R1_PINH1.1, TP15.TP, U2.8 (IO0), U3.3 (SQW/!INT)
IO/BOOT: BOOT_BUTTON.3, BOOT_BUTTON.4, C6.1, R_BOOT.1, U2.15 (IO9)
IO/CHANGE: C10.1, CHANGE_BUTTON.3, CHANGE_BUTTON.4, R_CHANGE.1, U2.23 (IO15)
MISO: D12.2, J4.P7 (DAT0), R8.1, TP6.TP, U1.2 (DO(IO1)), U2.27 (IO2)
MOSI: D11.2, J1.14, J4.P3 (CMD), R7.1, TP7.TP, U1.5 (DI(IO0)), U2.7 (IO7)
unnamed: J2.B5, R2-USB.1
unnamed: J2.A5, R2-USB1.2
unnamed: C1_BAT1.1, D2.1 (CATHODE), IC4.1 (VIN), IC4.3 (CE), Q1.2 (S)
unnamed: C4.1, D3.2 (A), D4.1 (K)
unnamed: MCP73831.1 (STAT), R1_BAT.2
unnamed: EPD_C1.2, J1.4
unnamed: MCP73831.5 (PROG), R2_BAT.2
unnamed: CHG_LED.C, R1_BAT.1
unnamed: EPD_C2.2, J1.5
unnamed: EPD_C8.2, J1.20
unnamed: EPD_C10.2, J1.22
unnamed: C_DELAY.1, IC1.5 (CT)
unnamed: EPD_C4.2, J1.24
unnamed: D7.1 (CATHODE), R_CAPACITOR.1
unnamed: EPD_C6.2, J1.18
unnamed: EPD_C7.2, J1.19
PREVGH: D5.1 (K), EPD_C9.2, J1.21
PREVGL: D4.2 (A), EPD_C3.2, J1.23
RESE: J1.3, Q3.2 (S), R3.2
RESE': R2.2, R3.1, SJ1.2
RESET: C5.1, IC1.1 (VOUT), RESET_BUTTON.3, RESET_BUTTON.4, R_RESET.1, U2.3 (EN)
RTC_RST: U2.16 (IO18), U3.4 (!RST)
RX: TP2.TP, U2.24 (RXD0/GPIO17)
SCK: D10.2, J1.13, J4.P5 (CLK), R6.1, TP8.TP, U1.6 (CLK), U2.6 (IO6)
SCL: J3.4, R2_PINH.1, SENSOR2.4 (SCK), U2.20 (IO22), U3.16 (SCL), U4.7 (SCL)
SDA: J3.3, R1_PINH.1, SENSOR2.3 (SDI), U2.19 (IO21), U3.15 (SDA), U4.8 (SDA)
SRC: C4.2, D5.2 (A), L1.1, Q3.3 (D)
SS_SD: D6.2, J4.P2 (CD/DAT3), R10.1, U2.4 (IO4)
TX: TP1.TP, U2.25 (TXD0/GPIO16)
USB_D+: D1.1 (I/O1_1), U2.14 (IO13)
USB_D-: D1.3 (I/O2_1), U2.13 (IO12)
VBAT: C2_BAT.1, MCP73831.3 (VBAT), Q1.3 (D), TP3.TP, U4.2 (CELL), U4.3 (VDD)
VBUS: C1_BAT.1, C4_USB.1, C5_USB.1, CHG_LED.A, D1.5 (VBUS), D2.2 (ANODE), MCP73831.4 (VIN), PFMF.050.1.2, Q1.1 (G), R1_PWRUSB.2, TP14.TP
VRTC: C8.1, C10_SUPERCAP.1, R_CAPACITOR.2, U3.14 (VBAT)
VUSB: J2.A4, J2.A9, J2.B4, J2.B9, PFMF.050.1.1

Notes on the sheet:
USB C connector & ESD protection
LDO Voltage Regulator
SD Card
Display Type Selector
E-Paper Drive Circuit
Li-Po Battery Charging Controller
ESP32 C6
E-Paper Display Header
EPD Power
Environmental Sensor BME688
Voltage Supervisor + Reset & Boot / IO Button
Battery Charge Level
RTC Module DS3231SN
Test Pads
Qwiic / Stemma QT
SPI ESD Protection Lines
External NOR Flash 64MB

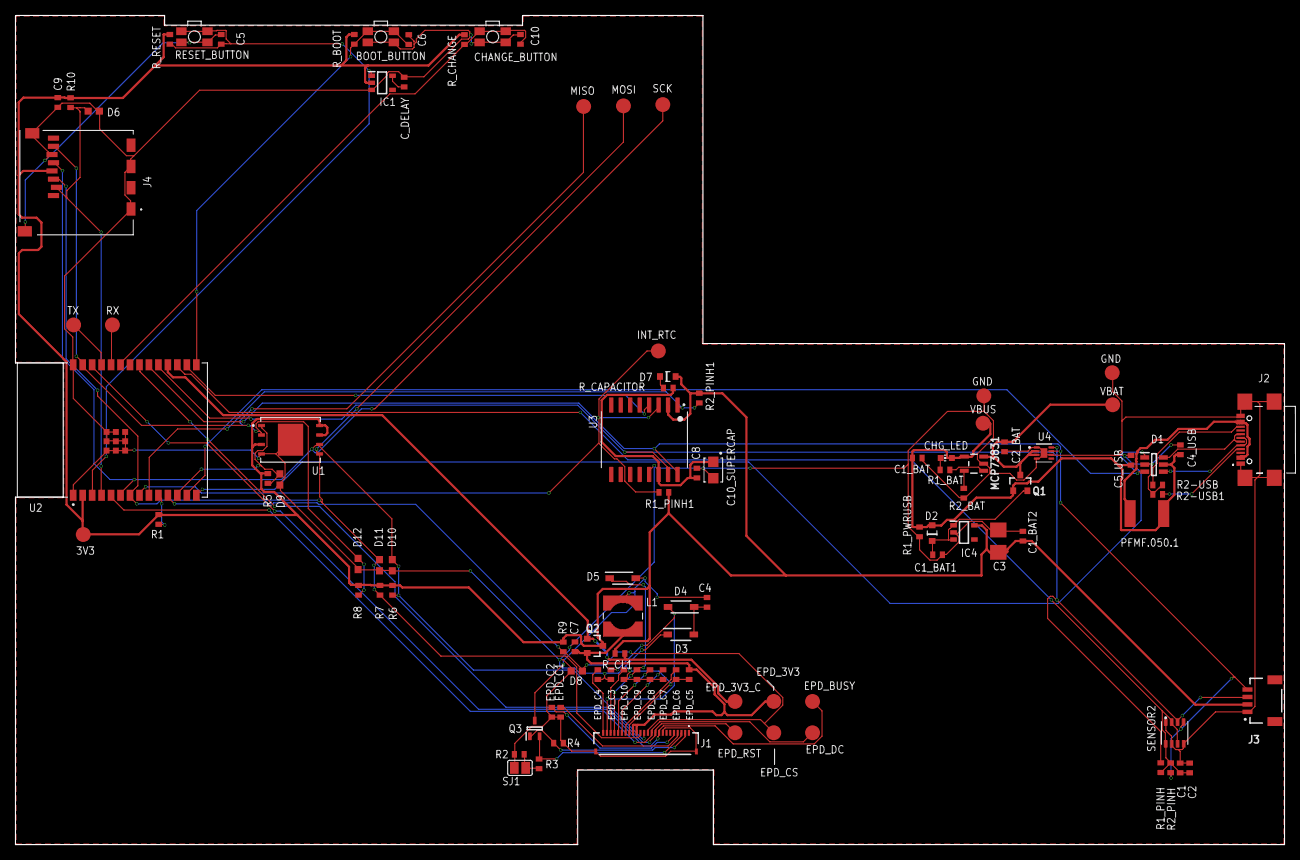
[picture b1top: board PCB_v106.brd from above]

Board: 2 copper layers, 170.2 x 111.2 mm, 103 parts (0 on the bottom side), 55 nets.

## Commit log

2025-04-06 Create LICENSE
2025-04-06 readme
2025-04-06 added hardware files
2025-04-06 Added manufacturing
2025-04-06 Adăugat BlockDiagram.png
2025-04-06 added mechanical
2025-04-06 Adăugat BlockScheme.png
2025-04-06 changed name
2025-04-06 deleted
2025-04-06 gata
2025-04-06 si readme
2025-04-11 am rezolvat issue urile plus am eliminat vias urile pe power lines
2025-04-11 pasii proiectului
2025-04-14 actualizare readme
2025-04-14 actualizare 2

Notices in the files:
parts and their libraries:
COPYRIGHT: Copyright (C) 2024 Ultra Librarian. All rights reserved.
